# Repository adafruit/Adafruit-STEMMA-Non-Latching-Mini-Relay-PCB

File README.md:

## Adafruit STEMMA Non-Latching Mini Relay PCB

<a href="http://www.adafruit.com/products/4409"><br/>
Click here to purchase one from the Adafruit shop</a>

PCB files for the Adafruit STEMMA Non-Latching Mini Relay. 

Format is EagleCAD schematic and board layout
* https://www.adafruit.com/product/4409

### Description

STEMMA plug-and-play parts make your next project soldering-free! This is the STEMMA Non-Latching Mini Relay. It gives you power to control, and control over power. Put simply, you can now turn on and off lamps, fans, solenoids, and other small appliances that run on up to 250VAC or DC power using any microcontroller or microcomputer, with ease.

No worrying about flyback diodes, level shifting, pin protection. The STEMMA board takes care of all that for you. You can use it with any 3V or 5V microcontroller/microcomputer.  To use with a breadboard, Raspberry Pi or Arduino, pair with a JST 3-pin to breadboard cable. If you want to use with a Circuit Playground or micro:bit, we have a cable with alligator clips.

* This  board has a single Signal pin (the white wire). Normally, the relay's COM pin is connected mechanically to the NC pin and the NO pin is disconnected.
* When the Signal pin is pulled high, the relay switches and the internal switch changes so that the COM pin is mechanically connected to the NO pin and NC is then disconnected
* When the relay is active, a red LED is lit, and about 50mA of current from the red power wire is used to keep the coil switched on. Note, if power is lost, the relay will go back 'open'.
* The connects for the relay are the white tubular thing at the far end of the PCB. You can poke wire into the holes, they will automatically grip onto wire that is 24AWG to 18AWG. Once you poke the wire in, give it a light pull to verify its clamped. To release the wire, use a thin screwdriver or pen to press on the button on the top while pulling the wire out.

You can switch up to 2A of resistive current at 30VDC or ~40VAC or lower. At 110VDC you can switch up to 0.3A, at 120VAC up to 0.5A, and at 250VAC you can switch up to 0.6A. Check the datasheet for the relay for the exact switching capacity, and of course, for reactive/inductive loads you will need to de-rate. This isn't a relay you can use to turn on and off your washer/dryer, stick to 60W or less.

Each STEMMA board comes with a fully assembled and tested PCB but no cable. No soldering is required to use it. There's an optional second switch on the side of the PCB, if you get a 3-pin terminal block you can solder that in place, but its optional.

Please note: If using with high voltages (> 24V) use care and common sense! High voltages require experience, and are only for use by engineers who are comfortable with guidelines and know how to use safely!
### License

Adafruit invests time and resources providing this open source design, please support Adafruit and open-source hardware by purchasing products from [Adafruit](https://www.adafruit.com)!

Designed by Limor Fried/Ladyada for Adafruit Industries.

Creative Commons Attribution/Share-Alike, all text above must be included in any redistribution. 
See license.txt for additional details.

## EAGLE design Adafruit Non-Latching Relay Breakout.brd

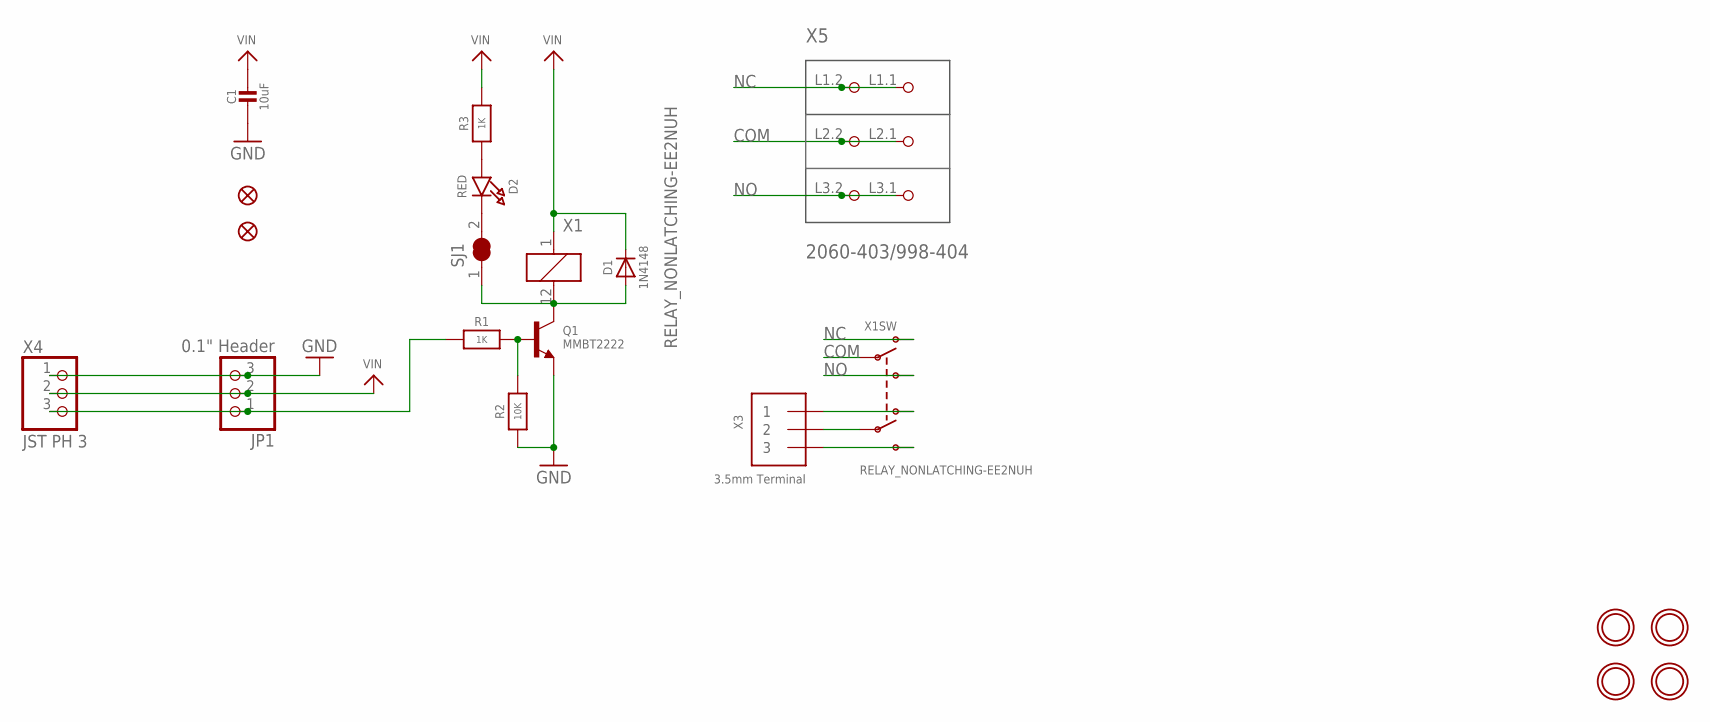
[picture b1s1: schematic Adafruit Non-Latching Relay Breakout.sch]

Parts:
C1: 10uF; 0805-NO
D1: 1N4148; SOD-323
D2: RED; CHIPLED_0805_NOOUTLINE
FID2, FID3: FIDUCIAL_1MM
JP1: 0.1" Header; 1X03_OVAL
Q1: MMBT2222; SOT23-R
R1, R3: 1K; 0603-NO
R2: 10K; 0603-NO
SJ1: SOLDERJUMPER_CLOSED; SOLDERJUMPER_CLOSEDWIRE
U$1, U$8, U$9, U$10: MOUNTINGHOLE2.5; MOUNTINGHOLE_2.5_PLATED
X1: RELAY_NONLATCHING-EE2NUH; RELAY_EE2_NOLATCH
X3: 3.5mm Terminal; TERMBLOCK_1X3-3.5MM
X4: JST PH 3; JSTPH3
X5: 2060-403/998-404; P-2060-403/998-404

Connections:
COM: X1.9 (P1), X5.L2.1 (P2.1), X5.L2.2 (P2.2)
GND: C1.2, JP1.3, Q1.2 (E), R2.1, X4.1
unnamed: D1.A, Q1.3 (C), SJ1.1, X1.12 (2)
unnamed: X1.3 (O2), X3.1
unnamed: X1.4 (P2), X3.2
unnamed: X1.5 (S2), X3.3
unnamed: Q1.1 (B), R1.2, R2.2
unnamed: D2.C, SJ1.2
unnamed: D2.A, R3.1
NC: X1.10 (O1), X5.L1.1 (P1.1), X5.L1.2 (P1.2)
NO: X1.8 (S1), X5.L3.1 (P3.1), X5.L3.2 (P3.2)
SIGNAL: JP1.1, R1.1, X4.3
VIN: C1.1, D1.C, JP1.2, R3.2, X1.1, X4.2

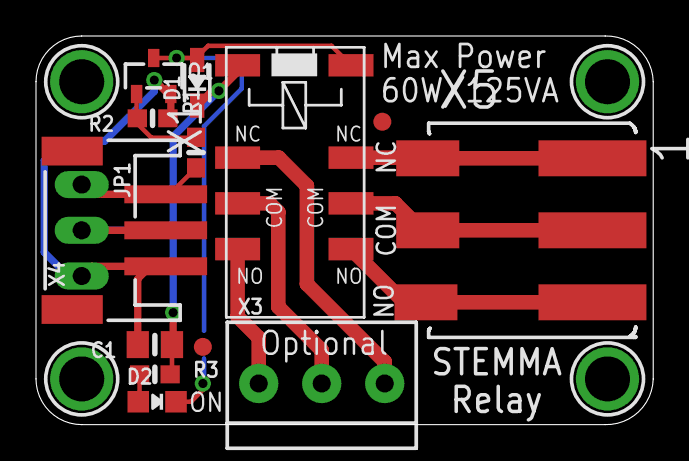
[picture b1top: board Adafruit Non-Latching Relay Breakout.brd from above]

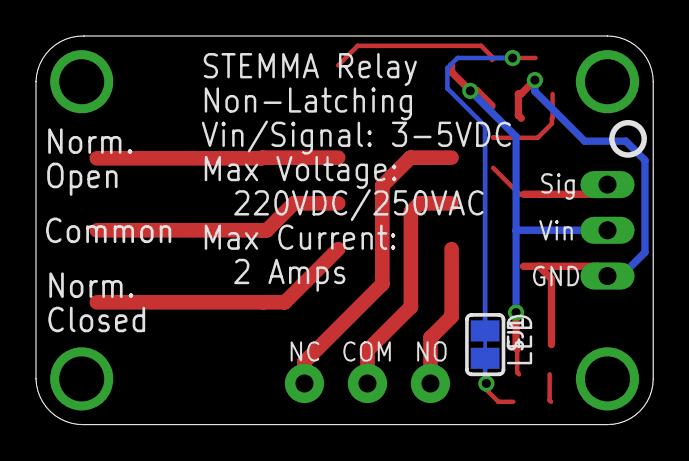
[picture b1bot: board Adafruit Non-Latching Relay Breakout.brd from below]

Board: 2 copper layers, 34.3 x 21.6 mm, 20 parts (2 on the bottom side), 13 nets.

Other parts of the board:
U$5: PCBFEAT-REV-040

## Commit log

2019-10-29 Adding board files.

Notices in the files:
parts and their libraries:
microbuilder: This work is placed in the public domain, and may be freely used for commercial and non-commercial work with the following conditions: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
